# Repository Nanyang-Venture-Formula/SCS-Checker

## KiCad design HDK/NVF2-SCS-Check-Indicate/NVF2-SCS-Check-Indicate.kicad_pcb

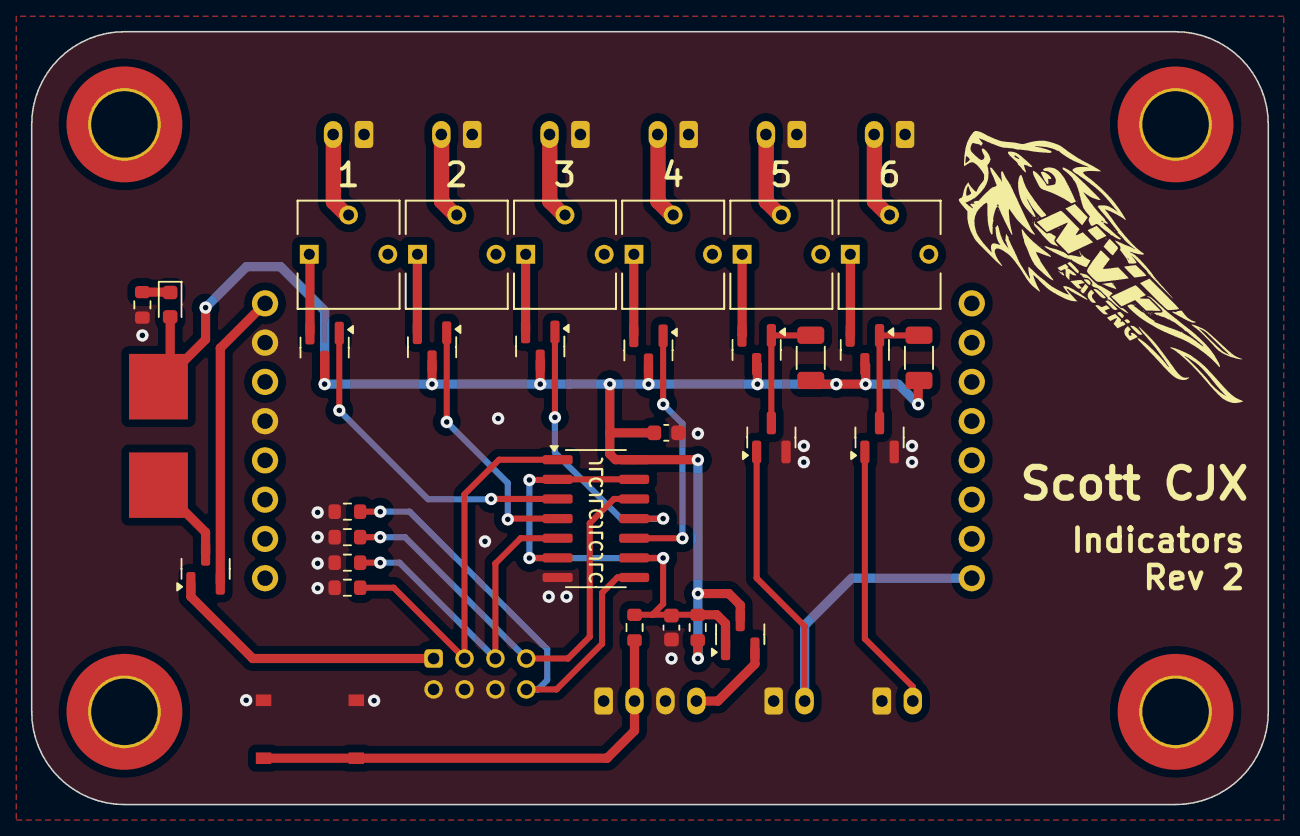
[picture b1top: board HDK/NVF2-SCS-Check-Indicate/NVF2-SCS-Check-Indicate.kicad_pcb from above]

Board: 2 copper layers, 80.0 x 50.0 mm, 42 parts (0 on the bottom side), 33 nets.

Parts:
C101, C102: 100n; C_0603_1608Metric
D101: BAV70; SOT-23
D102: LED; LED_0603_1608Metric
D103, D104, D105, D106, D107, D108: LED; PH_01x02H-H
F101: 0154008.DR; FUSE-Littelfuse_Nano2_154x
J101: SCS_IN; PHD_02x04H-H
J102, J103: Conn_01x02; PH_01x02H-H
Q101, Q102, Q103, Q104, Q105, Q106, Q108: BS250; SOT-23
Q107, Q109: 2N7002; SOT-23
R101, R102, R103, R104, R106: 10k; R_0603_1608Metric
R105: 200; R_0603_1608Metric
R107: 1k; R_0603_1608Metric
R108, R109: 120; R_1206_3216Metric
RV101, RV102, RV103, RV104, RV105, RV106: 10K; RV_Bourns_3362
SG101: Small-General BoardCut
SW101: SW_Push; PushBtn_TS-1187A-B-A-B
SW102: SW_Push_LED; PH_01x04H-H
U101: MC14070B; SOIC-14_3.9x8.7mm_P1.27mm

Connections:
+12V: C101.1, D102.2 (A), F101.2, Q101.3 (D), Q102.3 (D), Q103.3 (D), Q104.3 (D), Q105.3 (D), Q106.3 (D), Q108.3 (D), R106.1, R108.1, R109.1, U101.14 (VDD)
/LED_TEST+: Q106.2 (S), SW102.4 (A)
/SIG1: J101.3, R101.1, U101.1 (IN_1A)
/SIG2: J101.5, R102.1, U101.5 (IN_1B)
/SIG3: J101.7, R103.1, U101.12 (IN_1D)
/SIG4: J101.8, R104.1, U101.8 (IN_1C)
/SIG5: J102.2, Q107.1 (G), SG101.R8 (PB11)
/SIG6: J103.2, Q109.1 (G)
/SIG_TEST: R107.2, SW101.1, SW102.2
/~LED1: Q101.1 (G), U101.3 (OUTA)
/~LED2: Q102.1 (G), U101.4 (OUTB)
/~LED3: Q103.1 (G), U101.11 (OUTD)
/~LED4: Q104.1 (G), U101.10 (OUTC)
/~SIG_TEST: C102.1, Q106.1 (G), R106.2, R107.1, U101.2 (IN_2A), U101.6 (IN_2B), U101.9 (IN_2C), U101.13 (IN_2D)
GND: C101.2, C102.2, D103.1 (K), D104.1 (K), D105.1 (K), D106.1 (K), D107.1 (K), D108.1 (K), J101.2, J101.4, J101.6, J102.1, J103.1, Q107.2 (S), Q109.2 (S), R101.2, R102.2, R103.2, R104.2, R105.1, SG101.L2 (GND), SG101.L4 (GND), SW101.2, SW102.1, SW102.3 (K), U101.7 (VSS)
unnamed: D101.3 (K), F101.1
unnamed: D102.1 (K), R105.2
unnamed: D103.2 (A), RV101.2
unnamed: D104.2 (A), RV102.2
unnamed: D105.2 (A), RV103.2
unnamed: D106.2 (A), RV104.2
unnamed: D107.2 (A), RV105.2
unnamed: D108.2 (A), RV106.2
unnamed: Q101.2 (S), RV101.1
unnamed: Q102.2 (S), RV102.1
unnamed: Q103.2 (S), RV103.1
unnamed: Q104.2 (S), RV104.1
unnamed: Q105.1 (G), Q107.3 (D), R108.2
unnamed: Q105.2 (S), RV105.1
unnamed: Q108.1 (G), Q109.3 (D), R109.2
unnamed: Q108.2 (S), RV106.1
VBUS: D101.2 (A), SG101.L1 (V1)
VCC: D101.1 (A), J101.1

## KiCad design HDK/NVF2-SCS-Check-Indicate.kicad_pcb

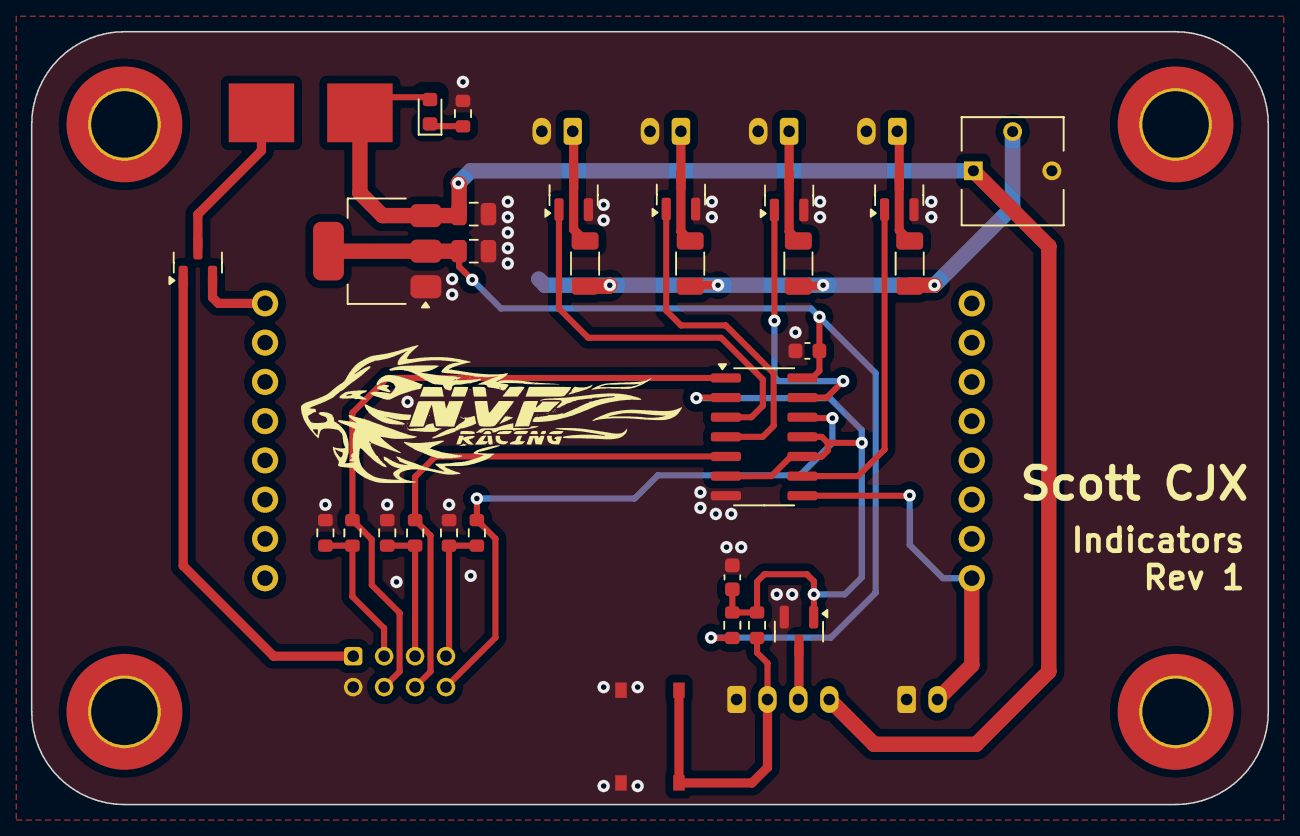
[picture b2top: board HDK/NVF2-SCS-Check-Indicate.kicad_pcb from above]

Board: 2 copper layers, 80.0 x 50.0 mm, 37 parts (0 on the bottom side), 26 nets.

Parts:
C101, C105: 100n; C_0603_1608Metric
C106, C107: 2u2; C_0805_2012Metric
D101: BAV70; SOT-23
D102: LED; LED_0603_1608Metric
F101: 0154008.DR; FUSE-Littelfuse_Nano2_154x
J101, J102, J103, J104, J106: Conn_01x02; PH_01x02H-H
J105: SCS_IN; PHD_02x04H-H
Q101, Q102, Q103, Q104, Q105: 2N7002; SOT-23
R101, R102, R103: 14k; R_0603_1608Metric
R106, R107, R108, R114: 10k; R_0603_1608Metric
R109: 200; R_0603_1608Metric
R110, R111, R112, R113: 120; R_1206_3216Metric
R115: 1k; R_0603_1608Metric
RV101: 10K; RV_Bourns_3362
SG101: Small-General BoardCut
SW101: SW_Push; PushBtn_TS-1187A-B-A-B
SW102: SW_Push_LED; PH_01x04H-H
U101: SOIC-14_3.9x8.7mm_P1.27mm
U105: AMS1117-5.0; SOT-223-3_TabPin2

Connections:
+5V: C101.1, C107.1, R114.1, U101.14 (VDD), U105.2 (VO)
+12V: C106.1, D102.2 (A), F101.2, RV101.1, SW102.4 (A), U105.3 (VI)
/LED_TEST-: Q105.3 (D), SW102.3 (K)
/SIG1: J105.4, R101.2, U101.1 (IN_1A)
/SIG1_N: J105.3, R101.1, R108.1
/SIG2: J105.6, R102.2, U101.5 (IN_1B)
/SIG2_N: J105.5, R102.1, R107.1
/SIG3: J105.8, R103.2, U101.12 (IN_2C)
/SIG3_N: J105.7, R103.1, R106.1
/SIG4: J106.2, SG101.R8 (PB11), U101.8 (IN_2D)
/SIG_TEST: R115.2, SW101.1, SW102.2
/~LED1: Q101.1 (G), U101.3 (OUTA)
/~LED2: Q102.1 (G), U101.4 (OUTB)
/~LED3: Q103.1 (G), U101.13 (OUTC)
/~LED4: Q104.1 (G), U101.9 (OUTD)
/~SIG_TEST: C105.1, Q105.1 (G), R114.2, R115.1, U101.2 (IN_2A), U101.6 (IN_2B), U101.10 (IN_1D), U101.11 (IN_1C)
GND: C101.2, C105.2, C106.2, C107.2, J101.2, J102.2, J103.2, J104.2, J105.2, J106.1, Q101.2 (S), Q102.2 (S), Q103.2 (S), Q104.2 (S), Q105.2 (S), R106.2, R107.2, R108.2, R109.1, RV101.3, SW101.2, SW102.1, U101.7 (VSS), U105.1 (GND)
unnamed: D101.3 (K), F101.1
unnamed: D102.1 (K), R109.2
unnamed: J101.1, Q101.3 (D), R110.2
unnamed: J102.1, Q102.3 (D), R111.2
unnamed: J103.1, Q103.3 (D), R112.2
unnamed: J104.1, Q104.3 (D), R113.2
VBUS: D101.2 (A), SG101.L1 (V1)
VCC: D101.1 (A), J105.1
V_{LED}: R110.1, R111.1, R112.1, RV101.2

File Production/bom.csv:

Designator,Footprint,Quantity,Value,LCSC Part #
"C101, C105",0603,2,100n,C14663
"C106, C107",0805,2,2u2,C377773
D101,SOT-23,1,BAV70,
D102,0603,1,LED,C434423
F101,FUSE-Littelfuse_Nano2_154x,1,0154008.DR,C206919
"J101, J102, J103, J104, J106",PH_01x02H-H,5,Conn_01x02,
J105,PHD_02x04H-H,1,SCS_IN,-
"Q101, Q102, Q103, Q104, Q105",SOT-23,5,2N7002,
"R101, R102, R103",0603,3,14k,
"R106, R107, R108, R114",0603,4,10k,C25804
R109,0603,1,200,C8218
"R110, R111, R112, R113",1206,4,120,C17909
R115,0603,1,1k,C21190
RV101,RV_Bourns_3362,1,10K,
SG101,Small-General BoardCut,1,~,-
SW101,PushBtn_TS-1187A-B-A-B,1,SW_Push, C318884
SW102,PH_01x04H-H,1,SW_Push_LED,-
U101,SOIC-14_3.9x8.7mm_P1.27mm,1,~,
U105,SOT-223-3_TabPin2,1,AMS1117-5.0,C6186

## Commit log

2024-03-06 Initialize gh-pages
2024-03-06 Moving files docs/* LICENSE using main
2024-03-06 Deploying to gh-pages from @ Nanyang-Venture-Formula/SCS-Checker@b6ddf042ae92ca111bb8071e8123559c2614a40c 🚀
2024-03-06 freeze rev1
2024-03-14 rev1
2024-03-14 Deploying to gh-pages from @ Nanyang-Venture-Formula/SCS-Checker@c22972e53480944f0c3e29b3692cce663e09193c 🚀
2024-03-18 updated docs
2024-03-18 fixed docs
2024-03-18 added script to fetch
2024-07-19 final rev2
